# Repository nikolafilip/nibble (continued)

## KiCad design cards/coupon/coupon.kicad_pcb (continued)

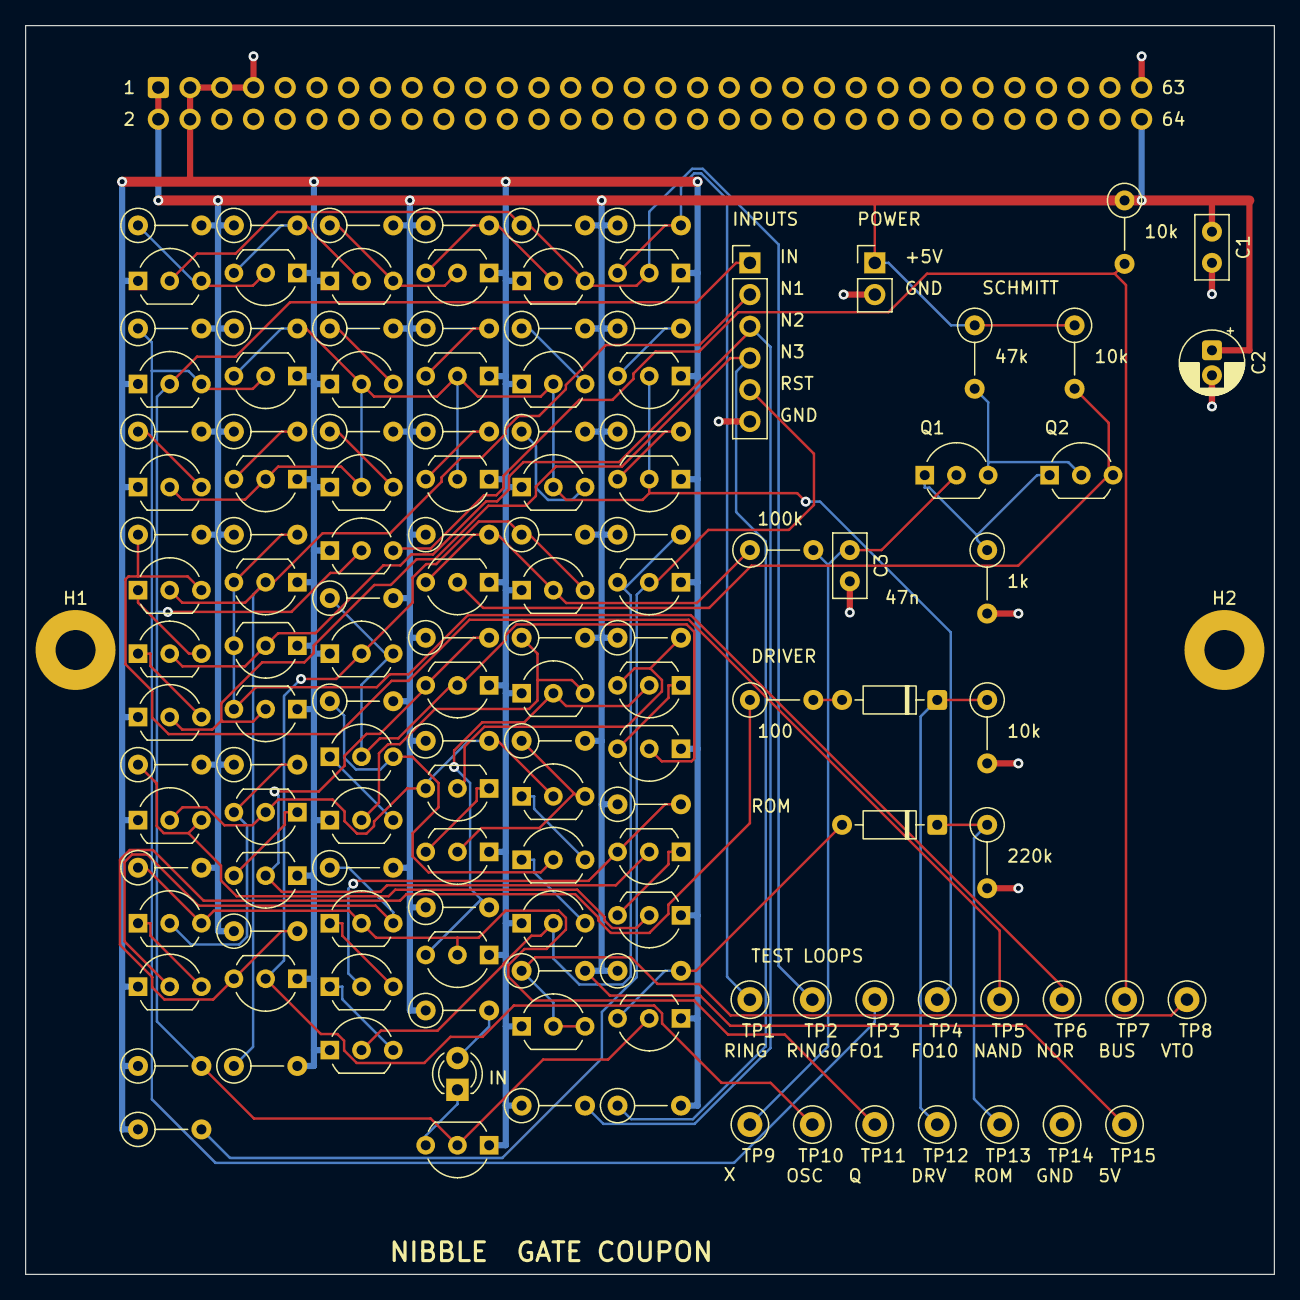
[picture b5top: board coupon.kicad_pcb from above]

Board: 2 copper layers, 100.0 x 100.0 mm, 136 parts (1 on the bottom side), 68 nets.

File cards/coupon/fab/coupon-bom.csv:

"Reference","Value","Footprint","QUANTITY"
"C1","100n","Capacitor_THT:C_Disc_D5.0mm_W2.5mm_P2.50mm","1"
"C2","10u","Capacitor_THT:CP_Radial_D5.0mm_P2.00mm","1"
"C3","47n","Capacitor_THT:C_Disc_D5.0mm_W2.5mm_P2.50mm","1"
"D1","LED","LED_THT:LED_D3.0mm","1"
"D2,D3","1N4148","Diode_THT:D_DO-35_SOD27_P7.62mm_Horizontal","2"
"J1","IN N1 N2 N3 RST GND","Connector_PinHeader_2.54mm:PinHeader_1x06_P2.54mm_Vertical","1"
"J2","+5V GND","Connector_PinHeader_2.54mm:PinHeader_1x02_P2.54mm_Vertical","1"
"J3","BUS","Connector_IDC:IDC-Header_2x32_P2.54mm_Vertical","1"
"Q1-Q57","2N7000","Package_TO_SOT_THT:TO-92_Inline_Wide","57"
"R1,R48,R52","10k","Resistor_THT:R_Axial_DIN0207_L6.3mm_D2.5mm_P5.08mm_Vertical","3"
"R2-R21,R23-R37,R47","47k","Resistor_THT:R_Axial_DIN0207_L6.3mm_D2.5mm_P5.08mm_Vertical","36"
"R22,R39","4.7k","Resistor_THT:R_Axial_DIN0207_L6.3mm_D2.5mm_P5.08mm_Vertical","2"
"R38,R41,R49","1k","Resistor_THT:R_Axial_DIN0207_L6.3mm_D2.5mm_P5.08mm_Vertical","3"
"R40","3.3k","Resistor_THT:R_Axial_DIN0207_L6.3mm_D2.5mm_P5.08mm_Vertical","1"
"R42-R46","1Meg","Resistor_THT:R_Axial_DIN0207_L6.3mm_D2.5mm_P5.08mm_Vertical","5"
"R50","100k","Resistor_THT:R_Axial_DIN0207_L6.3mm_D2.5mm_P5.08mm_Vertical","1"
"R51","100","Resistor_THT:R_Axial_DIN0207_L6.3mm_D2.5mm_P5.08mm_Vertical","1"
"R53","220k","Resistor_THT:R_Axial_DIN0207_L6.3mm_D2.5mm_P5.08mm_Vertical","1"
"TP1","TP_RING","TestPoint:TestPoint_Loop_D2.50mm_Drill1.0mm","1"
"TP2","RING0","TestPoint:TestPoint_Loop_D2.50mm_Drill1.0mm","1"
"TP3","TP_FO1","TestPoint:TestPoint_Loop_D2.50mm_Drill1.0mm","1"
"TP4","TP_FO10","TestPoint:TestPoint_Loop_D2.50mm_Drill1.0mm","1"
"TP5","TP_NAND","TestPoint:TestPoint_Loop_D2.50mm_Drill1.0mm","1"
"TP6","TP_NOR","TestPoint:TestPoint_Loop_D2.50mm_Drill1.0mm","1"
"TP7","TP_BUS","TestPoint:TestPoint_Loop_D2.50mm_Drill1.0mm","1"
"TP8","TP_VTO","TestPoint:TestPoint_Loop_D2.50mm_Drill1.0mm","1"
"TP9","X","TestPoint:TestPoint_Loop_D2.50mm_Drill1.0mm","1"
"TP10","TP_OSC","TestPoint:TestPoint_Loop_D2.50mm_Drill1.0mm","1"
"TP11","TP_Q","TestPoint:TestPoint_Loop_D2.50mm_Drill1.0mm","1"
"TP12","TP_DRV","TestPoint:TestPoint_Loop_D2.50mm_Drill1.0mm","1"
"TP13","TP_ROM","TestPoint:TestPoint_Loop_D2.50mm_Drill1.0mm","1"
"TP14","GND","TestPoint:TestPoint_Loop_D2.50mm_Drill1.0mm","1"
"TP15","+5V","TestPoint:TestPoint_Loop_D2.50mm_Drill1.0mm","1"

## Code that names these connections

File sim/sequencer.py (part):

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Header in : M0..M7 (program memory word), CF, ZF (from the ALU), CLK, RST.
Header out: II, PCE and the 19 matrix-driven control lines SUB EO AI AO BI BO BA AB OI IO FI HLT MAI MI MO ONE F0 F1 INP.
Bus       : BUS0..3# driven (open drain) with OPR3..0 while IO is high.
Link out  : OPR0..7, PCR, RAI (PCL goes over the bus header, pin 51).

Steps (one-hot T0..T4, master-slave flip-flops with asynchronous reset): S0 II, S1 PCE, S2 OPI+PCE (two-word
instructions only), S3 and S4 the matrix rows; DONE returns to S0. IR (4) and OPR (8) are transparent latches open
while their load line and PH1 are both high, so they capture the memory word during the low half of the clock and
are closed before the rising edge. The flags are the same kind of latch, open during FI.
"""
import nmos
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        'XOR':({'F0','F1','EO','AI','FI','DONE'},set()),'LDI':({'IO','AI','DONE'},set()),'JMP':({'PCL','DONE'},set()),
        'JC':({'DONE'},set()),'JZ':({'DONE'},set()),'LOAD':({'IO','MAI'},{'MO','AI','DONE'}),'STORE':({'IO','MAI'},{'AO','MI','DONE'}),
        'CALL':({'RAI','PCL','DONE'},set()),'JNZ':({'DONE'},set()),'JNC':({'DONE'},set())}
LINK=['OPR0','OPR1','OPR2','OPR3','OPR4','OPR5','OPR6','OPR7','PCR','RAI']     # PCL is a header line (pin 51)

GROUP_TITLES={
 'clock':'TWO-PHASE CLOCK (as on the register board): PH1 opens masters and latches while CLK is low, PH2 copies to slaves while CLK is high.  RSTN for the asynchronous resets.',
 'steps':'STEP COUNTER, one-hot: T0N (0 = step S0, so reset lands in S0), T1..T4.  Next state: S0 -> S1; S1 -> S2 if the opcode is two-word (TWO) else S3; S2 -> S3; S3 -> S4 unless DONE; S4 or DONE -> S0.  II = T0, PCE = T1 or T2, OPI = T2.',
 'ir':'INSTRUCTION REGISTER (4 bits, the opcode) and OPERAND REGISTER (8 bits): transparent latches.  IR and OPR3..0 open while II and PH1; OPR7..4 open while OPI and PH1.  They close before the rising edge.',
 'opdec':'OPCODE DECODER: IR3..0 -> OP0#..OP15# (active low), through a pair of 2-to-4 predecoders so no NAND has more than two transistors in series.  TWO = JMP or JC or JZ or CALL or JNZ or JNC.',
 'famdec':'FAMILY DECODER: OPR3..0 -> F0#..F15#, the member of the opcode-0000 family.',
 'flags':'FLAGS: CFQ, ZFQ latched from the ALU while FI and PH1.  Only ADD SUB INC DEC AND OR XOR assert FI.',
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 'cols':'COLUMN BUFFERS (D041): the diode node of each column has a 1 Meg pull-down and feeds one inverter; a second inverter (22k) drives the control line, so the line falls through a transistor in microseconds instead of decaying through 1 Meg into every board and the ribbons.',
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    d.inputs={f'M{i}' for i in range(8)}|{'CF','ZF','CLK','RST'}
    d.group='clock'
    d.inv('CLKN','CLK'); d.inv('RSTN','RST',pu='10k')          # RSTN reaches every flip-flop and latch
    d.nor('PH1','CLK','PH2',pu='10k'); d.nor('PH2','CLKN','PH1',pu='10k')
    # ---- step counter ----
    d.group='steps'
    d.nor('T0N_D','DONE','T4')                                   # next is S0 when DONE, or after S4
    d.ff('T0N','T0N_D',ckn='PH1',ckb='PH2',rstn='RSTN'); d.inv('T0','T0N',pu='22k')
    d.ff('T1','T0',ckn='PH1',ckb='PH2',rstn='RSTN')
    d.nand('T2D_N','T1','TWO'); d.inv('T2_D','T2D_N')
    d.ff('T2','T2_D',ckn='PH1',ckb='PH2',rstn='RSTN')
    d.nand('T3_A','T1','TWON'); d.inv('T2N','T2'); d.nand('T3_D','T3_A','T2N')   # T1.TWON + T2
    d.ff('T3','T3_D',ckn='PH1',ckb='PH2',rstn='RSTN',qpu='22k')
    d.inv('DONEN','DONE'); d.nand('T4D_N','T3','DONEN'); d.inv('T4_D','T4D_N')
    d.ff('T4','T4_D',ckn='PH1',ckb='PH2',rstn='RSTN',qpu='22k')
    d.inv('T3N','T3',pu='10k'); d.inv('T3NB','T3',pu='10k'); d.inv('T4N','T4',pu='10k')        # feed every row: 10k for the fan-out, T3 split in two; T4N feeds 14 rows since D040
    # ---- IR, OPR ----
    d.group='ir'
    d.nand('ENIRN','T0','PH1'); d.inv('ENIR','ENIRN')              # II = T0
    d.nor('IIOPIN','T0','T2'); d.inv('IIOPI','IIOPIN'); d.nand('ENOLN','IIOPI','PH1'); d.inv('ENOL','ENOLN')
    d.nand('ENOHN','T2','PH1'); d.inv('ENOH','ENOHN')
    for i in range(4): d.latch(f'IR{i}',f'M{i+4}','ENIR',rstn='RSTN')
    for i in range(4): d.latch(f'OPR{i}',f'M{i}','ENOL',rstn='RSTN',qpu='22k')
    for i in range(4,8): d.latch(f'OPR{i}',f'M{i}','ENOH',rstn='RSTN')
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    decoder(d,'FD_',['OPR0','OPR1','OPR2','OPR3'],'F')
    # ---- flags ----
    d.group='flags'
    d.nand('ENFN','FI','PH1'); d.inv('ENF','ENFN')
    d.latch('CFQ','CF','ENF',rstn='RSTN'); d.latch('ZFQ','ZF','ENF',rstn='RSTN')
    # ---- rows ----
    d.group='rows'
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
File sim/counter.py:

"""Board 09: the program counter (8 bits) and the return register (8 bits).
Header in : PCE, PCL, CLK, RST.   Header out: PC0..PC7.
Link in   : OPR0..7, PCR, RAI from the sequencer (D035).
PC: every bit is a master-slave flip-flop whose input is one of  PC xor carry (count, or hold when PCE=0),
OPR (PCL: jump, call) or RA (PCR: return).  The count carry ripples: t0 = PCE, t(i+1) = t(i) and PC(i).
RA: eight transparent latches open while RAI and PH1: they capture the old PC during the low half of the
CALL's execute tick, and close before the edge on which PC loads the target.
"""
import nmos

GROUP_TITLES={
 'clock':'TWO-PHASE CLOCK and RSTN (as on the register and sequencer boards)',
 'sel':'INPUT SELECT: LOADN = neither PCL nor PCR: the counter counts (or holds) unless a load line is high',
 'carry':'COUNT CARRY CHAIN: t0 = PCE, t(i+1) = t(i) and PC(i).  Bit i toggles when t(i) is 1.',
 'pc':'PROGRAM COUNTER: D = LOADN.(PC xor t) + PCL.OPR + PCR.RA, then a master-slave flip-flop with reset',
 'ra':'RETURN REGISTER: transparent latches open while RAI and PH1',
 'leds':'INDICATORS: PC7..0, RA7..0',
}

def build():
    d=nmos.Design('counter')
    d.inputs={'PCE','CLK','RST','PCL','PCR','RAI'}|{f'OPR{i}' for i in range(8)}
    d.group='clock'
    d.inv('CLKN','CLK'); d.inv('RSTN','RST',pu='10k')
    d.nor('PH1','CLK','PH2',pu='10k'); d.nor('PH2','CLKN','PH1',pu='10k')
    d.group='sel'
    d.nor('LOADN','PCL','PCR',pu='22k')
    d.group='carry'
    t='PCE'
    for i in range(7):
        d.nand(f'TC{i+1}N',t,f'PC{i}'); d.inv(f'TC{i+1}',f'TC{i+1}N'); t=f'TC{i+1}'
    d.group='pc'
    for i in range(8):
        t='PCE' if i==0 else f'TC{i}'
        d.xor(f'PX{i}',f'PC{i}',t)
        d.nand(f'PD{i}_1','LOADN',f'PX{i}'); d.nand(f'PD{i}_2','PCL',f'OPR{i}'); d.nand(f'PD{i}_3','PCR',f'RA{i}')
        d.nand(f'PD{i}',f'PD{i}_1',f'PD{i}_2',f'PD{i}_3')
        d.ff(f'PC{i}',f'PD{i}',ckn='PH1',ckb='PH2',rstn='RSTN',qpu='22k')
    d.group='ra'
    d.nand('ENRAN','RAI','PH1'); d.inv('ENRA','ENRAN',pu='22k')
    for i in range(8): d.latch(f'RA{i}',f'PC{i}','ENRA',rstn='RSTN')
    d.group='leds'
    for n in [f'PC{i}' for i in range(7,-1,-1)]+[f'RA{i}' for i in range(7,-1,-1)]: d.led('LED_'+n,n)
    for i in range(8): d.ext_loads[f'PC{i}']+=2      # the memory boards' address compare, the panel LED
    return d

CARD_TITLES=dict(GROUP_TITLES)
CARD_TITLES['carry']='COUNT CARRY: t(i) comes from the card below over the link (PCE on bit 0); t(i+1) = t(i) and PC(i) goes to the card above.  Bit i toggles when t(i) is 1.'
CARD_TITLES['leds']='INDICATORS: PC, RA'

def build_bit(i):
    """Counter bit card i (D042): PC bit i (flip-flop with its count / load mux) and RA bit i (latch), with the card's own
    clock phases, RSTN, LOADN and the RA enable. Bus: PCE, PCL, CLK, RST in; PC<i> out. The sequencer's link ribbon
    (2x6, chained along the eight cards) brings OPR<i>, PCR, RAI; the count carry runs card to card over a 2x3 link:
    TC<i> in (PCE on bit 0), TC<i+1> out (nothing on bit 7). Same nets as the full board."""
    d=nmos.Design(f'ctr{i}')
    d.inputs={'PCE','CLK','RST','PCL','PCR','RAI',f'OPR{i}'}|({f'TC{i}'} if i else set())
    d.group='clock'
    d.inv('CLKN','CLK'); d.inv('RSTN','RST',pu='10k')
    d.nor('PH1','CLK','PH2',pu='10k'); d.nor('PH2','CLKN','PH1',pu='10k')
    d.group='sel'
    d.nor('LOADN','PCL','PCR',pu='22k')
    t='PCE' if i==0 else f'TC{i}'
    d.group='carry'
    if i<7: d.nand(f'TC{i+1}N',t,f'PC{i}'); d.inv(f'TC{i+1}',f'TC{i+1}N')
    d.group='pc'
    d.xor(f'PX{i}',f'PC{i}',t)
    d.nand(f'PD{i}_1','LOADN',f'PX{i}'); d.nand(f'PD{i}_2','PCL',f'OPR{i}'); d.nand(f'PD{i}_3','PCR',f'RA{i}')
    d.nand(f'PD{i}',f'PD{i}_1',f'PD{i}_2',f'PD{i}_3')
    d.ff(f'PC{i}',f'PD{i}',ckn='PH1',ckb='PH2',rstn='RSTN',qpu='22k')
    d.group='ra'
    d.nand('ENRAN','RAI','PH1'); d.inv('ENRA','ENRAN',pu='22k')
    d.latch(f'RA{i}',f'PC{i}','ENRA',rstn='RSTN')
    d.group='leds'
    for n in [f'PC{i}',f'RA{i}']: d.led('LED_'+n,n)
    d.ext_loads[f'PC{i}']+=2                              # the memory cards' address compare, the panel LED
    if i<7: d.ext_loads[f'TC{i+1}']+=3                    # the next card: its xor (two gates) and its carry NAND
    return d

if __name__=='__main__':
    d=build(); print(d.check()); print('board: transistors',d.ntransistors(),'resistors',d.nresistors(),'leds',d.nleds())
    for i in (0,3,7):
        d=build_bit(i); print(d.check()); print(f'bit {i} card: transistors',d.ntransistors(),'resistors',d.nresistors(),'leds',d.nleds())

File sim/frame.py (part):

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
def header_gnd(w,hx,hy,outward,y_gnd_trunk=None):
    """Pre-route the bus header's GND pins (3,4,5,7,63) for a header placed at (hx,hy) rot 90 and turned onto the back
    (bus.hole: the odd pins are the upper row). outward=-1 if the header is at the top edge, +1 at the bottom."""
    P=lambda n:bus.hole(hx,hy,n)
    (x4,y4),(x8,y8),(x3,y3),(x50,y50)=P(3),P(7),P(4),P(bus.N-1)
    w.rails.append(('GND','F.Cu',x4,y4,x8,y8,0.5))        # 3-5-7 along the upper row
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    xr,yend=min(rails,key=lambda r:abs(r[0]-x3))
    w.rails.append(('GND','B.Cu',x3,y3,x3,ylink,0.5)); w.rails.append(('GND','B.Cu',x3,ylink,xr,ylink,0.5)); w.rails.append(('GND','B.Cu',xr,yend,xr,ylink,0.5))

LINK=['OPR0','OPR1','OPR2','OPR3','OPR4','OPR5','OPR6','OPR7','PCR','RAI','GND','GND']   # the sequencer-counter link header (D035), pins 1..12
def link_header(w,x,y,direction,pins=LINK,value="LINK",note=None,used=None):
    """IDC link header (2x6 for 12 pins, 2x3 for 6) carrying signals between neighbouring boards: the operand register
    and the counter's load lines (D035), a bit card's carry and zero chain (D042). pins: the signal per pin 1..n, GND
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    (xa,ya),(xb,yb)=P(2),P(1); w.rails.append(('+5V','F.Cu',xa,ya,xb,yb,0.5))
    for n in (2,64):
        px,py=P(n)
        near=[r[2] for r in w.rails if r[1]=='B.Cu' and abs(r[2]-r[4])<0.01 and abs(r[2]-px)<0.7]     # a tile rail under the pin's column (the sequencer's 10.16 pitch puts one at 89.0)
        if near:    # jog 1.5 mm past the rail before dropping to the trunk
            xj=near[0]+1.5; w.rails.append(('+5V','B.Cu',px,py,px,py+2.0,0.5)); w.rails.append(('+5V','B.Cu',px,py+2.0,xj,py+3.5,0.5)); w.rails.append(('+5V','B.Cu',xj,py+3.5,xj,yv,0.5)); w.vias.append(('+5V',xj,yv))
        else: w.rails.append(('+5V','B.Cu',px,py,px,yv,0.5)); w.vias.append(('+5V',px,yv))
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LINK_IN_HX,LINK_OUT_HX=14.0,80.0
LINK_HCOL=72.0                     # tiles must end above the link headers' courtyard (y 88.8)
def link_gnd(w,hx,pins):
    """Pre-route every GND pin of a link header at (hx, LINK_HY) rot 90 to its own via: the top row 2.5 mm up, the bottom
    row 2.5 mm down. The pour then never has to reach under the header (on memslot it did not, and the stitch found no spot)."""
    for n,sig in enumerate(pins,1):
        if sig!='GND': continue
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
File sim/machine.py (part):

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        b,_,dev=spec.partition('@')
        if b in ('clk','clkc'):       # the clock board or card: RUN switch closed, pot at minimum, timing capacitor empty at power-up
            ports,sub=subckt(b,export(b,dev=='dev'),corner,rng,seed)
            body=["Rrun +5V RUNSW 1m","Rpot RT X 1m","Rj2 Net-_J2-Pin_2_ 0 1G"]+(["Rhd HLT HLTD 100k","Chd HLTD 0 2.2n"] if dev=='dev' else [])      # the RC on HLT is drawn on the sheet (D050)
            if HOLD and not any(hold_off(l) for l in sub):      # (a card that has the two parts gets no second pair)
                hm={'TYP':'2N7000','LO':'2N7000_LO','HI':'2N7000_HI'}; body+=["Rhold X XH 100",f"Mhold XH RST GND {hm[random.Random(seed+1000).choice(['LO','TYP','HI'])] if corner=='MIX' else hm[corner]}"]      # a draw of its own: every other transistor keeps the model it has without the hold-off
            L+=sub[:-1]+body+[sub[-1]]; L.append(f"X{b} "+" ".join(ports)+f" {b}"); L.append(f".ic V(x{b}.X)=0 V(x{b}.POR)={POR_V0:g}")      # both capacitors empty (POR_V0 shifts the release): the card's power-on reset resets the machine
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                nodes=set(tok for l in sub[1:-1]+body for tok in l.split()[1:]); ports=[x for x in bus.SIGNALS if x in nodes]
                L+=[f".subckt prog{p} "+" ".join(ports)]+sub[1:-1]+body+[sub[-1]]; L.append(f"Xprog{p} "+" ".join(ports)+f" prog{p}")
            continue
        if b=='progc':     # one program card per four words, jumpers strapped to the card's addresses (PC7..2 = c), switches set from the program
            import json
            ncards=max(1,(len(program)+3)//4); mp=json.load(open(os.path.join(BOARDS,'..','cards','prog','prog.map.json')))
            for c in range(ncards):
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    rows=[]
    for k in range(nticks):
        if k<len(det): tt=det[k]-5e-6; edge=1
        else: tt=t[-1]-5e-6; edge=0      # the halted state: the run ends at tend, or 7 ms after HLT with the real clock
        r={p:bit(p,tt) for p in probes}; r['edge']=edge; r['t']=tt; rows.append(r)
    return rows, det

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        if 'OI' in c: known['out']=True
        if 'seq' in boards:
            chk['step']=(s['step'],[row[f'xseq.T{i}'] for i in range(5)].index(1) if 1 in [row[f'xseq.T{i}'] for i in range(5)] else -1)
            if 'FI' not in s['ctl']:     # the flag latches are transparent while FI and PH1: during that tick they already show the new flags
                chk['cf']=(s['cf'],row['xseq.CFQ']); chk['zf']=(s['zf'],row['xseq.ZFQ'])
        for f,(want,got) in chk.items():
            if want!=got: bad.append((k,f,want,got))
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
